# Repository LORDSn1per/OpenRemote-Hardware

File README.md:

# OpenRemote Rev6 Hardware

OpenRemote Rev6 is an open-source, offline smart remote based on the excellent [OMOTE hardware](https://github.com/OMOTE-Community/OMOTE-Hardware). It combines a 2.8-inch capacitive touchscreen with physical buttons, infrared, Wi-Fi, Bluetooth, an ESP32-S3, expandable storage, and a fully 3D-printable enclosure.

Rev6 focuses on making the remote easier to source, nicer to print, more serviceable, and ready for dock charging—while retaining support for the original Adafruit display.

> **Firmware:** [OpenRemote Firmware](https://github.com/LORDSn1per/OpenRemote-Firmware)

## What is new in Revision 6?

- **New IPS display support.** Rev6 supports the EastRising/BuyDisplay ER-TFT028A2-4 capacitive display with a separate six-pin touch FPC. It is brighter, sharper, has much better viewing angles, is still in production, and is free of the ghost-touch problem that affected the original screen.
- **Original display compatibility.** The discontinued Adafruit Product 2770/CH280QV10-CT display remains fully supported, and the Rev6 firmware includes an option that runs it with zero ghost touches.
- **Built-in microphone.** A rear-mounted digital I2S microphone provides hardware support for voice control, voice search, and future assistant features.
- **Faster charging.** The TP4056 charging circuit is configured for up to approximately 1 A, subject to the battery, power source, and thermal conditions.
- **Dock charging input.** Rev6 includes a dedicated 5 V input before the fuse, feeding the pogo-pin charging dock contacts or any other 5 V source.
- **Improved serviceability.** Five rear-installed M3 × 8 mm screws secure the PCB and enclosure, making the remote easier to assemble and reopen.
- **Updated PCB branding.** The board is now branded OpenRemote and includes a QR code linking directly to the firmware repository.

## New BuyDisplay LCD

### Why the display changed

Two things forced the move away from the original Adafruit screen:

1. **It is discontinued.** The Adafruit Product 2770 / CH280QV10-CT is no longer in production. Anyone building a remote today is hunting through dwindling stock and resellers, which is no basis for a project people are meant to be able to build.
2. **Its touch behaviour could make the remote unusable.** The Adafruit panel is subject to a well-known ghost-touch problem — phantom presses the user never made. On a remote control that is not a cosmetic annoyance: the device wakes by itself, fires commands at your equipment, and drains its own battery.

The recommended Rev6 screen is therefore the 2.8-inch 240×320 EastRising/BuyDisplay IPS TFT with capacitive touch. It is in current production, easier to source, brighter and sharper, has far better viewing angles, and does not suffer the ghost-touch fault. Its separate six-pin touch cable connects to the new J6 connector on the Rev6 PCB.

### The Adafruit display still works — with zero ghost touches

If you already own the Adafruit panel, it is not wasted. The Rev6 firmware includes an option that changes how the Adafruit touch panel is handled, and with it enabled the display produces **zero ghost touches**. It is a fully supported configuration, not a fallback, and it is why the Adafruit cover plate and matching printed parts are still published here.

Choose your display on this basis:

- **Building from scratch, or buying a screen now** — use the BuyDisplay panel. It is the current, in-production part.
- **Already have the Adafruit panel** — use it, enable the Adafruit touch option in the firmware, and print the Adafruit cover plate.

Either way, set the correct display option in the [OpenRemote firmware](https://github.com/LORDSn1per/OpenRemote-Firmware) before use.

### Fitting

The BuyDisplay assembly is approximately **0.8 mm thicker** than the original Adafruit screen. It therefore requires the newly updated BuyDisplay front cover plate. Do not try to force the thicker display into the original Adafruit cover.

Printable parts are split by display, so each folder contains a complete, matched set:

- [`CAD/BuyDisplay LCD/`](CAD/BuyDisplay%20LCD) — use **`Cover Plate 5mm (+1mm) Rev6-v37.stl`** with the new BuyDisplay screen.
- [`CAD/Adafruit LCD/`](CAD/Adafruit%20LCD) — use **`Cover Plate 4mm (+0mm) Rev6-v37.stl`** with the original Adafruit screen.

Each folder also carries a **Bambu Lab 3MF project** prepared for multicolour printing.

| BuyDisplay screen | New and original screens |
|:---:|:---:|
|  |  |

## Redesigned printed buttons

The Rev6 button system has been redesigned for a cleaner, more professional finish:

- The button grid now prints as **two interlocking halves** that click together.
- Separating the grid makes multicolour button graphics easier to print cleanly.
- Button faces are now completely smooth.
- The old physical cut-outs used to form button icons have been removed.
- Icons and labels can instead be printed directly into the smooth button surfaces for sharper graphics and a much nicer feel.
- The supplied Bambu Lab 3MF project contains the prepared colour-printing setup.

## Rear-case options

The Rev6 enclosure is available with two rear-shell choices:

1. **Normal rear case** — the standard shell for USB-C charging (`Case - Screws and No Pogo Pins Rev6-v37.stl`).
2. **Pogo-pin rear case** — adds two charging contacts for the self-aligning charging dock (`Case - Screws with Pogo Pins Rev6-v37.stl`).

The spring-loaded pogo pins live in the dock; the remote carries fixed gold-plated contacts, so there is nothing sprung to wear out in the handheld part.

## Charging dock

<div align="center">
  
</div>

The Rev6 charging dock is a self-aligning cradle that charges the remote through the pogo-pin rear case, and doubles as an always-on IR and sub-GHz blaster in its own right.

- **Pogo-pin charging.** Two spring-loaded pins meet the fixed contacts in the pogo rear case, so the remote charges by being set down rather than plugged in.
- **Independent ESP32-C3.** An ESP32-C3 Super Mini gives the dock its own Wi-Fi and Bluetooth, so it can act while the remote is asleep or away from the cradle.
- **Four-emitter IR blaster.** Four MHL512IR059CRT 940 nm emitters run in parallel, each through its own 39 Ω 0.5 W resistor, switched by an FS8205A dual MOSFET. Designed for roughly 95 mA per emitter in pulsed remote-control service, giving the dock far more IR reach than the handheld unit.
- **433 MHz sub-GHz radio.** A CC1101 module on SPI adds control of RF devices that infrared cannot reach — blinds, garage doors, and similar.
- **Status LED and button.** A tactile button on GPIO3 with hardware debounce, plus a status indicator.
- **Powered by USB-C.** The dock is powered solely through the USB-C connector on the ESP32-C3 module. The 2-pin JST header (J1) is not a second power input — it carries the 5 V rail out to the pogo pins.
- **Serviceable.** A 45 × 60 mm two-layer PCB on a 37 × 52 mm M3 mounting pattern, with a separate printed base lid.
- **Smart-home relay.** Because the board has its own Wi-Fi it can hold a permanent connection to Home Assistant, an MQTT broker or Homebridge, and act on the remote's behalf while the remote sleeps. That is a firmware capability rather than a hardware one — see the [firmware repository](https://github.com/LORDSn1per/OpenRemote-Firmware) — but it is the reason the dock carries an ESP32-C3 rather than a charging circuit alone.

> **Firmware note:** the IR bank is sized for pulsed use. Firmware must not hold `IR_PWM` high continuously.

### Dock files

- Printable parts: [`CAD/Dock/STL`](CAD/Dock/STL) — dock shell, base lid, and menu button, plus a Bambu Lab 3MF project in [`CAD/Dock`](CAD/Dock).
- Fusion source: [`CAD/Charging Dock Rev6-v47.f3z`](CAD/Charging%20Dock%20Rev6-v47.f3z)
- KiCad source: [`PCB/Dock Rev6`](PCB/Dock%20Rev6) — includes its own [project README](PCB/Dock%20Rev6/README.md) covering footprints, sourcing notes, and the Fusion handoff transform.
- Production files: [Gerber and drill ZIP](PCB/Dock%20Rev6/Production%20Files/gerber.zip), [CPL](PCB/Dock%20Rev6/Production%20Files/CPL.csv) and [BOM](PCB/Dock%20Rev6/Production%20Files/BOM.xlsx) for JLCPCB assembly of the SMD parts. The through-hole parts — ESP32-C3 headers, CC1101, IR LEDs, resistors, button, J1 and C6 — are fitted by hand.

## PCB files

The complete KiCad source is in [`PCB/Revision 6`](PCB/Revision%206). Custom symbols, footprints, and 3D models are included with the project.

The exact production files prepared for the Rev6 manufacturing order are here:

- [Gerber and drill ZIP](PCB/Revision%206/PCB%20Production%20Files/gerber.zip)
- [Component placement list (CPL)](PCB/Revision%206/PCB%20Production%20Files/CPL.csv)
- [Bill of materials (BOM)](PCB/Revision%206/PCB%20Production%20Files/BOM.xlsx)

The PCB is a two-layer design. The production set was exported using the **EastRising Capacitive LCD** assembly variant. The original Adafruit display remains represented in the KiCad project as an alternate variant.

> MIC1, the microphone module, does not currently have a JLCPCB/LCSC placement code in the production BOM. Source and fit it separately if your assembler cannot supply it.

## Core hardware features

- ESP32-S3 with Wi-Fi and Bluetooth
- 2.8-inch 240×320 capacitive touchscreen
- Physical navigation, media, volume, channel, activity, and colour buttons
- High-power infrared output
- MicroSD storage
- Motion-based wake support
- Built-in I2S microphone
- USB-C charging
- Pogo-pin dock charging
- Fully local operation with no mandatory cloud service

## Building the remote

1. Order the Rev6 PCB using the supplied Gerber ZIP, BOM, and CPL.
2. Source the selected LCD and use its matching front cover plate.
3. Print the enclosure and buttons. For multicolour printing, use the supplied Bambu Lab 3MF project.
4. Fit a suitable protected 3.7 V LiPo battery with the correct JST polarity.
5. Install the PCB and secure the assembly using five M3 × 8 mm screws.
6. Flash the latest [OpenRemote firmware](https://github.com/LORDSn1per/OpenRemote-Firmware).

Always verify component orientation, battery polarity, display selection, and the manufacturer preview before ordering assembled PCBs.

## Project status

The Rev6 remote PCB has been manufactured and assembled, and the first unit is running. The normal and pogo-pin rear cases and both display cover plates are complete and published.

The charging dock's enclosure parts are complete and published. Its PCB has been corrected — the ESP32-C3 Super Mini now mounts on the underside of the board — and a new set of fabrication files is published. The corrected dock board has not yet been built and tested, so check the manufacturer preview carefully before ordering.

## Credits

OpenRemote builds on the original open-source [OMOTE](https://github.com/OMOTE-Community) hardware project. Thank you to the OMOTE contributors and community for creating the foundation that made OpenRemote possible.

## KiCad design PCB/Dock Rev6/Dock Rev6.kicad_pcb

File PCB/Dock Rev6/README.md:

# OpenRemote Dock Rev6 KiCad Project

This is a self-contained KiCad 10 project starter for the OpenRemote Rev6 charging dock.

## Included footprints and 3D models

| Library footprint | Intended hardware | Interface / package |
|---|---|---|
| `ESP32-C3_SuperMini_Header_2x08_P2.54mm` | ESP32-C3 Super Mini shown by the owner | Two 1x8 headers, 2.54 mm pitch; owner-supplied STEP model |
| `CC1101_433MHz_Coil_Module_2x04_P2.54mm` | 28x15 mm CC1101 433 MHz module, spring antenna version | 2x4 header, 2.54 mm pitch |
| `LED_5mm_Side_Mount_C405273` | Meihua MHL512IR059CRT IR LED, LCSC C405273 | THT, 5 mm, horizontal/side mounting |
| `FS8205A_SOT-23-6` | FUXINSEMI FS8205A, LCSC C908265 | SOT-23-6 |
| `HX-XH2.54-2PZZ_C42391660` | hanxia HX-XH2.54-2PZZ, LCSC C42391660 | Vertical shrouded 1x2 male header; vendor land pattern is 2.50 mm pitch |
| `SW_6x6x5H_THT` | 6x6 mm tactile switch, 5 mm body height | Four-pin THT |
| `LED_5mm_Green_THT` | Standard green 5 mm LED | THT, 2.54 mm pitch |

The ESP32 model is the owner's supplied `esp32 c3 supermini.step`, copied into the project as `ESP32-C3_SuperMini.step`. The project also includes `ESP32-C3_SuperMini_2x08_Header.step`: two 2.24 mm-high black 1x8 header blocks with 16 gold pins. All STEP files are project-local, so no Downloads or global KiCad 3D-model path is required.

## Important sourcing notes

- The ESP module follows the owner's supplied **16-pin ESP32-C3 Super Mini** image: 18x22.52 mm with two 1x8, 2.54 mm header rows. It does not use the different 18-pin Waveshare C3-Zero footprint from the earlier retail link.
- J1 is the exact hanxia HX-XH2.54-2PZZ sold as LCSC C42391660. LCSC describes it as 2.54 mm, but its manufacturer-linked EasyEDA land pattern uses 2.50 mm pad pitch, 1.0 mm drills, and a 7.5 x 5.9 mm shrouded body; the project follows that land pattern.
- CC1101 clone modules vary. This footprint follows the common 28x15 mm, 2x4 2.54 mm module and the pin order shown in the provided image. Check the delivered module before ordering the PCB.
- `Dock Rev6.kicad_pcb` uses a 45x60 mm main body with narrow front and rear tongues. The confirmed physical rear tongue ends at dock Z=`-68.0 mm`; it is straight between the two rear receivers and has no obsolete scallops.
- The owner confirmed that the provisional handoff reversed the physical faces. The installed-board mapping is now **physical dock Z = KiCad Y - 140 mm**: Fusion Z=`-70` is the rear and Z=`+30` is the front.
- U1 is centred at KiCad `(100.00, 82.39)` with USB-C facing the physical rear and is placed on `B.Cu`. The ESP32 module hangs below the host PCB; the black header plastic lies between the ESP32 board and the host PCB, as it will when assembled with female header sockets. It was moved 1.5 mm into the cavity so the module PCB clears the rear wall. Its exact 18 mm body has approximately 0.50 mm lateral clearance to each physical rear lid receiver.
- The four large `User.Drawings` circles are the exact **15 mm OD physical receiver outlines**, mirrored into the confirmed board coordinates. Rear centres are KiCad `(82.998, 80.858)` and `(117.002, 80.858)`; front centres are `(83.643, 161.292)` and `(116.357, 161.292)`.
- In Fusion, `Dock + Correct Rear USB-C Opening Base Feature` was removed and the retained master body was restored as the visible solid `Dock - User Editable Shell (No Cutouts)`. This leaves the enclosure apertures for the owner to sketch and cut directly without deleting the dock shell.
- The final exact-solid Fusion audit reports **no collision between the underside ESP32/header assembly and the base lid or its bosses**. The lowest point of the ESP32 model is 0.294 mm above the flat lid surface. The USB, button, and LED apertures are intentionally left for the owner to create before enclosure release.
- Four 3.3 mm NPTH M3 mounting holes are on an exact 37x52 mm pattern at dock X/Z `(+/-18.5, +6)` and `(+/-18.5, -46)`. Each hole has an R4 mm all-copper keepout. H1-H4 are locked `board_only` footprints, excluded from BOM and position files, so **Update PCB from Schematic will not delete them again**.
- The matching Fusion base lid has four 7.5 mm OD bosses at those same centres. Each boss has a 2.55 mm blind pilot, an 8.0 mm PCB seating plane, and 3.4 mm thread engagement for an M3x5 screw through this 1.6 mm board. The original pre-boss lid body is retained hidden for rollback.

## Pin order

CC1101 pads are numbered by rows as shown in the supplied diagram: `1 GND`, `2 VCC`, `3 GDO0`, `4 CSN`, `5 SCK`, `6 MOSI`, `7 MISO/GDO1`, `8 GDO2`.

ESP32-C3 Super Mini pad numbers use the printed signal names directly. USB-C is at the top: left row `5V`, `GND`, `3V3`, `GPIO4/SCK/A4`, `GPIO3/A3`, `GPIO2/A2`, `GPIO1/A1`, `GPIO0/A0`; right row `GPIO5/MISO/A5`, `GPIO6/MOSI`, `GPIO7/SS`, `GPIO8/SDA`, `GPIO9/SCL`, `GPIO10`, `GPIO20/RX`, `GPIO21/TX`.

## Electrical design

- CC1101 SPI: `GPIO4 SCK`, `GPIO5 MISO`, `GPIO6 MOSI`, `GPIO7 CSN`; interrupts are `GPIO10 GDO0` and `GPIO20 GDO2`.
- Four MHL512IR059CRT emitters are connected in parallel through individual `39R 0.5W` resistors. GPIO0 drives both paralleled halves of Q1 through `100R`, with a `100k` gate pulldown.
- The 39R IR branches are designed for pulsed remote-control service at approximately 95mA per LED from 5V. Firmware must not hold `IR_PWM` high continuously.
- The green status LED uses GPIO1 and `1k`. The tactile button uses GPIO3 with a `10k` pull-up and `100nF` hardware debounce.
- ESP32-C3 strap pins GPIO2, GPIO8, and GPIO9 are deliberately left unconnected; GPIO21 is also reserved.
- Added decoupling: `100nF + 10uF` at the ESP 5V input, `100nF + 10uF` at the CC1101 3.3V rail, and `100uF + 100nF` at the pulsed IR bank.

### Pogo-pin output protection

`F1` is a 1 A resettable polyfuse (PPTC, LCSC C220146,
`DockRev6:Fuse_1206_3216Metric_Pad1.42x1.75mm_HandSolder`) in series between the `+5V`
rail and `J1` pin 1, creating the `POGO_5V` net. It is the same part the remote uses as
its F1. The IR bank, the ESP32 and the decoupling all stay on the raw `+5V` rail; only
the pogo output passes through the fuse.

**It is in the schematic only — it is not yet placed or routed on the PCB.**

This replaced an earlier BAT20J series diode, for two reasons. A polyfuse actually
addresses the failure being guarded against: if the exposed pogo contacts are shorted,
it heats and trips, where a series diode would simply conduct and let the rail collapse.
And it barely drops any voltage — a few tens of millivolts against roughly 0.45 V for a
Schottky at 1 A — so the remote still sees close to a full 5 V.

Two things to be aware of:

- A polyfuse does **not** block reverse current. The dropped diode would have stopped
  the remote back-feeding into the dock; the fuse does not. If back-feed matters, an
  ideal-diode controller or a load switch would cover both cases.
- Trip is thermal, so it takes seconds rather than being instant, and hold current
  derates as temperature rises. With the remote's TP4056 set near 1 A, a 1 A hold part
  sits close to its limit inside a closed enclosure. Watch for nuisance trips during a
  full-rate charge; a 1.1 A or 1.5 A hold part is the fallback.

### Capacitor placement

- `C1 100nF`: immediately beside U1's 5V/GND header pins; shortest possible loop.
- `C2 10uF`: beside U1 and C1 on the 5V rail; C1 should be closer than C2.
- `C3 100nF`: immediately beside U2 pins 2 VCC and 1 GND; this is the most placement-sensitive radio capacitor.
- `C4 10uF`: beside U2 and C3; C3 should be closer than C4.
- `C5 100nF`: beside U1 GPIO3 and pull-up R1, at the controller end of the BUTTON trace.
- `C6 100uF`: beside Q1/J1 at the high-current IR power entry/current loop.
- `C7 100nF`: beside Q1/J1 and C6, with the shortest 5V-to-GND loop; C7 should be closer to the switching loop than C6.

`Dock Rev6.kicad_pcb` is populated but not routed. The remaining SMD parts are staged by circuit: C1/C2 beside the header-mounted ESP32, C5/R1 immediately left of it, C3/C4 beside the CC1101 power pins, R3/R4/Q1 to the left of the CC1101 coil envelope, C7 beside J1, and R2 beside D5. The current DRC reports silkscreen cleanup warnings plus the expected unrouted nets; it does not report a copper short, hole, or board-edge clearance failure.

The `.before-*` rollback boards, the DRC/ERC reports, the netlist and the exported schematic PDF have been removed; only the current `Dock Rev6.kicad_pcb` and `Dock Rev6.kicad_sch` are kept. Earlier states remain in git history if a rollback is ever needed. `apply_mechanical_fit_v3.py` reapplies the final U1 position and rear-tongue geometry without altering nets or component identities. Use KiCad's native refill after running it. Do not run `generate_dock_rev6_mechanical_board.py` on the populated board; that generator creates a blank mechanical PCB and would replace component placement.

## Fusion 3D handoff

`Dock Rev6 PCB Assembly.step` is the current board-plus-components model handed to
Fusion. Regenerate it with `export_dock_rev6_step.py`, which runs:

```
kicad-cli pcb export step --subst-models --no-dnp --force
```

No origin flag is passed, so the STEP keeps KiCad's absolute board coordinates
(substrate spans X `77.5`-`122.5`, Y `-166.0`-`-72.0`, Z `0`-`1.6`). The Fusion
placement transform depends on that:

```
dock X =  step X - 100 mm
dock Y =  step Z + 8 mm      (PCB seating plane on the base-lid bosses)
dock Z = -step Y - 140 mm    (owner-confirmed mirrored physical face)
```

`CAD/FusionScripts/DockRev6PCBReplace` deletes any existing `Dock Rev6 PCB*`
occurrence, re-imports this STEP at that transform as the component
`Dock Rev6 PCB`, then re-runs the solid interference check against `Dock:1` and
`Dock Base Lid:1` and writes `CAD/Dock Rev6/Charging Dock Rev6 PCB Replace Report.json`.
Base-lid interference is a failure; dock-shell interference at SW1, J1, D1-D5 is
expected until the owner cuts the USB, button, and LED apertures.

`Dock Rev6 Component Staging.step` is the superseded 26 Aug 16:52 export, taken
before power/ground routing was finalised and before SW1 moved to the
`SW-TH_KH-6X6X5H-ZJ` (C2837541) model and J1 to `HX-XH2.54-2PZZ` (C42391660). It
is kept only for rollback; Fusion should no longer import it.

`Dock Rev6 PCB Assembly Preview.png` and `Dock Rev6 PCB Assembly Preview Bottom.png`
are `kicad-cli pcb render` views of the same board state.

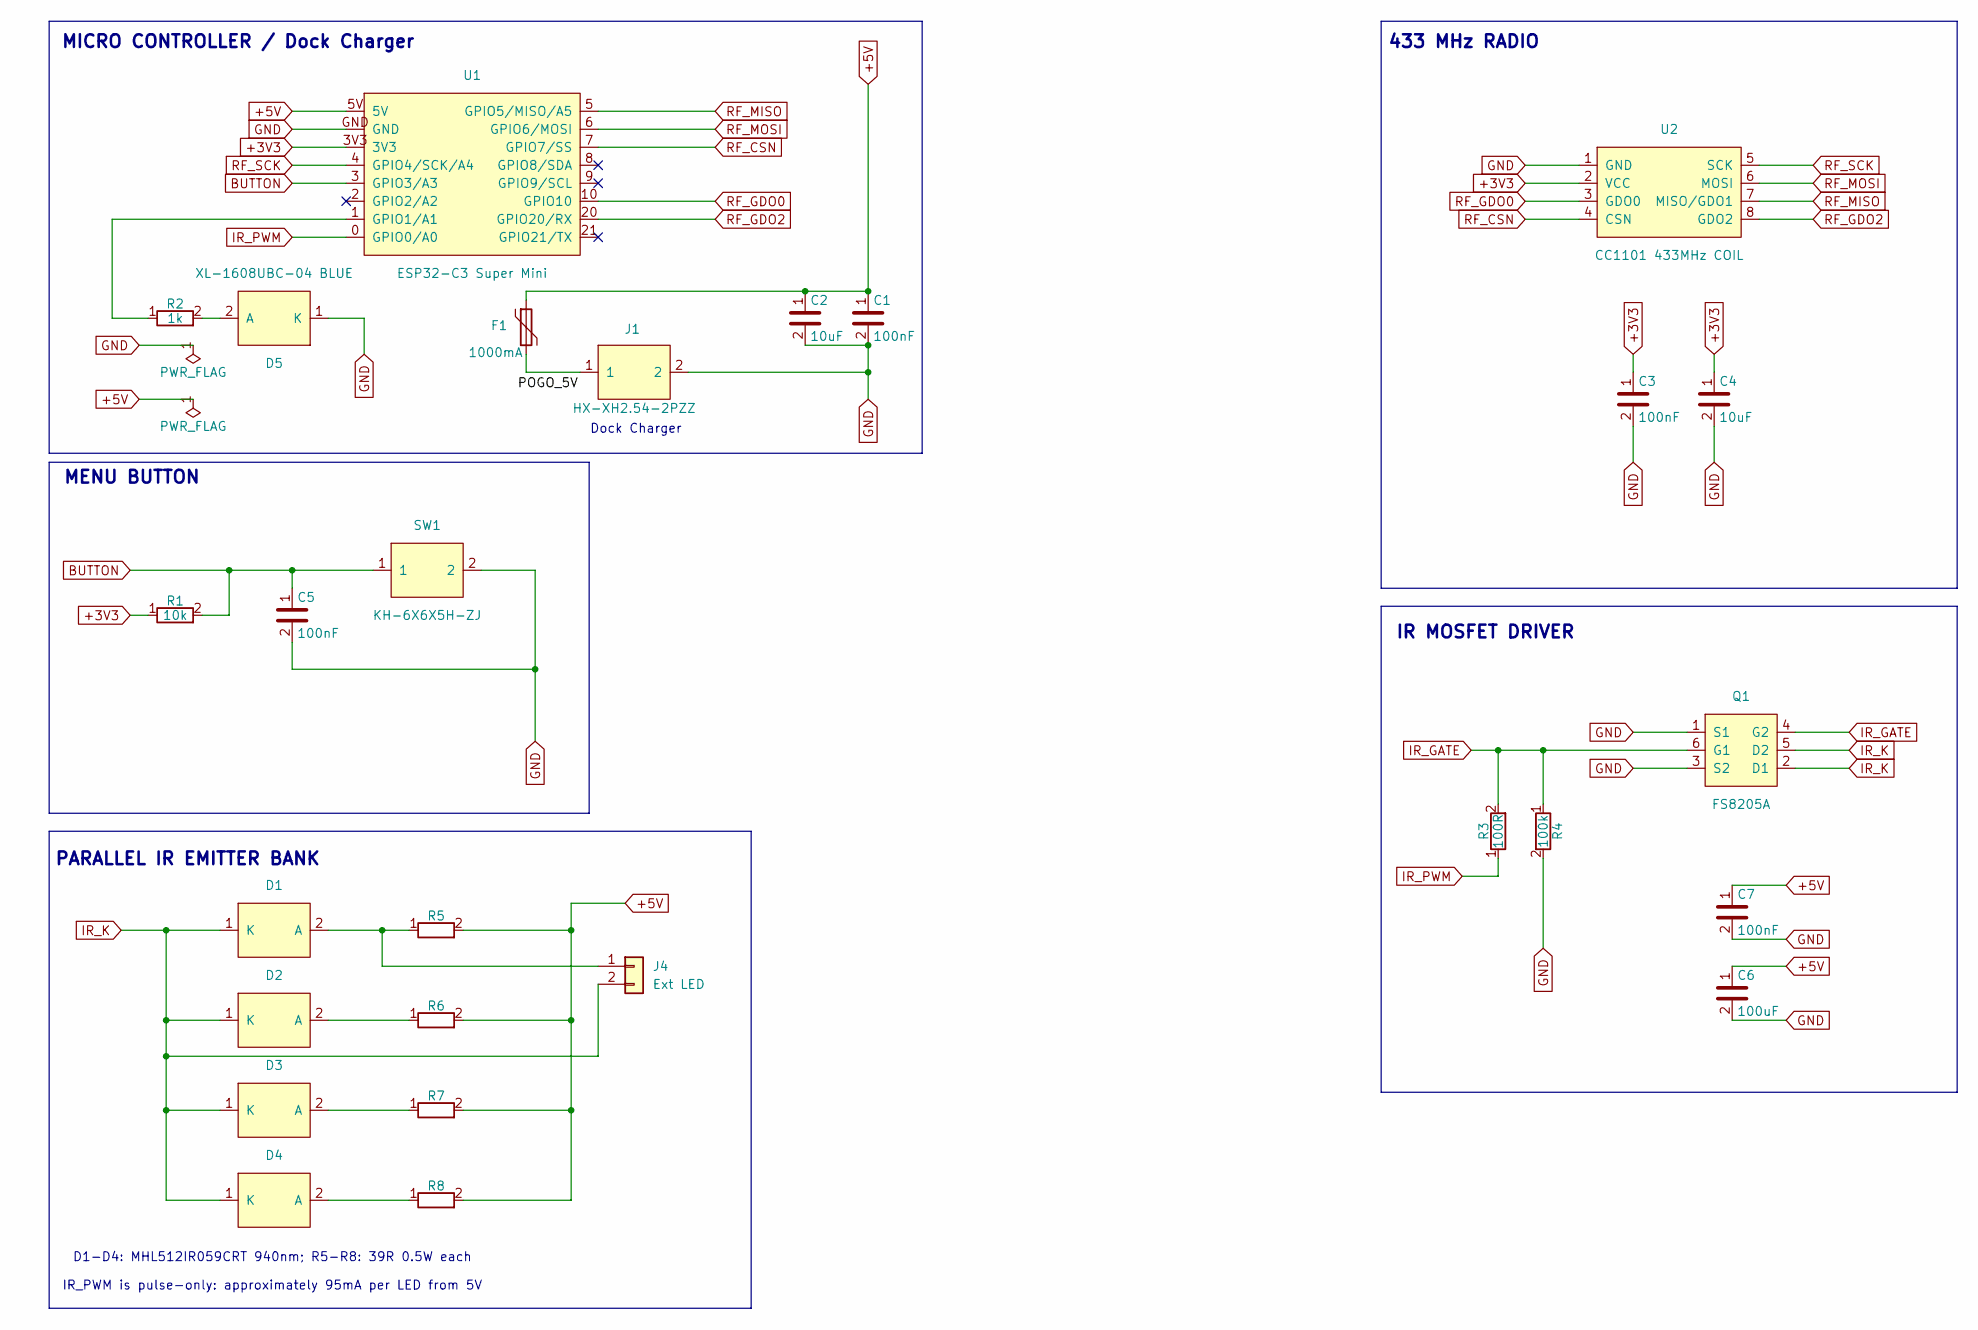
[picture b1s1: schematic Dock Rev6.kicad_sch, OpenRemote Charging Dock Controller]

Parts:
C1, C3, C5, C7: 100nF; C_0603_1608Metric
C2, C4: 10uF; C_0805_2012Metric
C6: 100uF; CP_Radial_D5.0mm_P2.50mm
D1: MHL512IR059CRT 940nm; IR_LED_THT_D1_with_Assembly3D
D2, D3, D4: MHL512IR059CRT 940nm; LED_5mm_Green_THT
D5: XL-1608UBC-04 BLUE; LED_0603_1608Metric_NoSilk; LCSC C965807
F1: 1000mA; Fuse_1206_3216Metric_Pad1.42x1.75mm_HandSolder; LCSC C220146
J1: HX-XH2.54-2PZZ; HX-XH2.54-2PZZ_C42391660
J4: Ext LED; R_0508_1220Metric_Pad1.12x2.15mm_HandSolder
Q1: FS8205A; FS8205A_SOT-23-6
R1: 10k; R_0603_1608Metric
R2: 1k; R_0603_1608Metric
R3: 100R; R_0603_1608Metric
R4: 100k; R_0603_1608Metric
R5, R6, R7, R8: 39R 0.5W; R_Axial_DIN0411_L9.9mm_D3.6mm_P15.24mm_Horizontal
SW1: KH-6X6X5H-ZJ; SW-TH_KH-6X6X5H-ZJ
U1: ESP32-C3 Super Mini; ESP32-C3_SuperMini_Header_2x08_P2.54mm
U2: CC1101 433MHz COIL; CC1101_433MHz_Coil_Module_2x04_P2.54mm

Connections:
+3V3: C3.1, C4.1, R1.1, U1.3V3, U2.2 (VCC)
+5V: C1.1, C2.1, C6.1, C7.1, F1.1, R5.2, R6.2, R7.2, R8.2, U1.5V
BUTTON: C5.1, R1.2, SW1.1, U1.3 (GPIO3/A3)
GND: C1.2, C2.2, C3.2, C4.2, C5.2, C6.2, C7.2, D5.1 (K), J1.2, Q1.1 (S1), Q1.3 (S2), R4.2, SW1.2, U1.GND, U2.1 (GND)
IR_GATE: Q1.4 (G2), Q1.6 (G1), R3.2, R4.1
IR_K: D1.1 (K), D2.1 (K), D3.1 (K), D4.1 (K), J4.2, Q1.2 (D1), Q1.5 (D2)
IR_PWM: R3.1, U1.0 (GPIO0/A0)
unnamed: D1.2 (A), J4.1, R5.1
unnamed: D2.2 (A), R6.1
unnamed: D3.2 (A), R7.1
unnamed: D4.2 (A), R8.1
unnamed: D5.2 (A), R2.2
unnamed: F1.2, J1.1
unnamed: R2.1, U1.1 (GPIO1/A1)
RF_CSN: U1.7 (GPIO7/SS), U2.4 (CSN)
RF_GDO0: U1.10 (GPIO10), U2.3 (GDO0)
RF_GDO2: U1.20 (GPIO20/RX), U2.8 (GDO2)
RF_MISO: U1.5 (GPIO5/MISO/A5), U2.7 (MISO/GDO1)
RF_MOSI: U1.6 (GPIO6/MOSI), U2.6 (MOSI)
RF_SCK: U1.4 (GPIO4/SCK/A4), U2.5 (SCK)

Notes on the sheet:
PARALLEL IR EMITTER BANK
D1-D4: MHL512IR059CRT 940nm; R5-R8: 39R 0.5W each
IR MOSFET DRIVER
IR_PWM is pulse-only: approximately 95mA per LED from 5V
MENU BUTTON
433 MHz RADIO
Dock Charger
MICRO CONTROLLER / Dock Charger

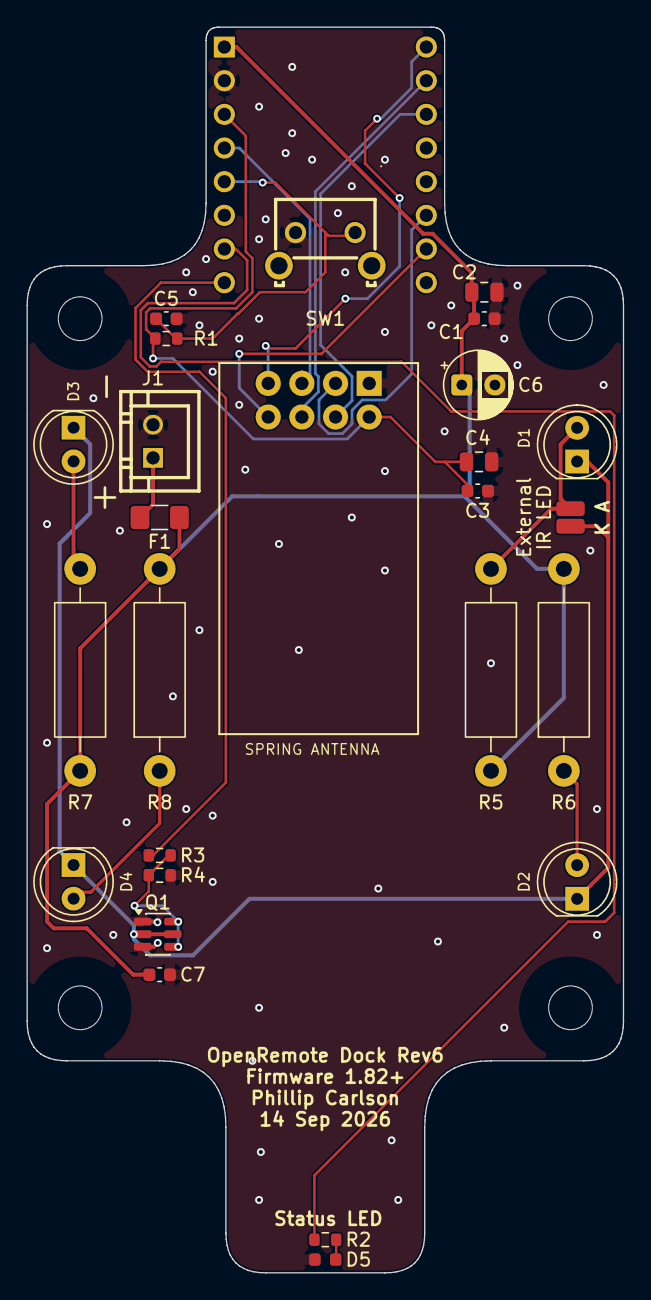
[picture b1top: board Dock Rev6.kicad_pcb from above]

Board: 2 copper layers, 45.0 x 94.0 mm, 31 parts (1 on the bottom side), 20 nets.

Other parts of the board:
H1, H2, H3, H4: M3x5 PCB SCREW / 3.3mm NPTH; MountingHole_3.2mm_M3

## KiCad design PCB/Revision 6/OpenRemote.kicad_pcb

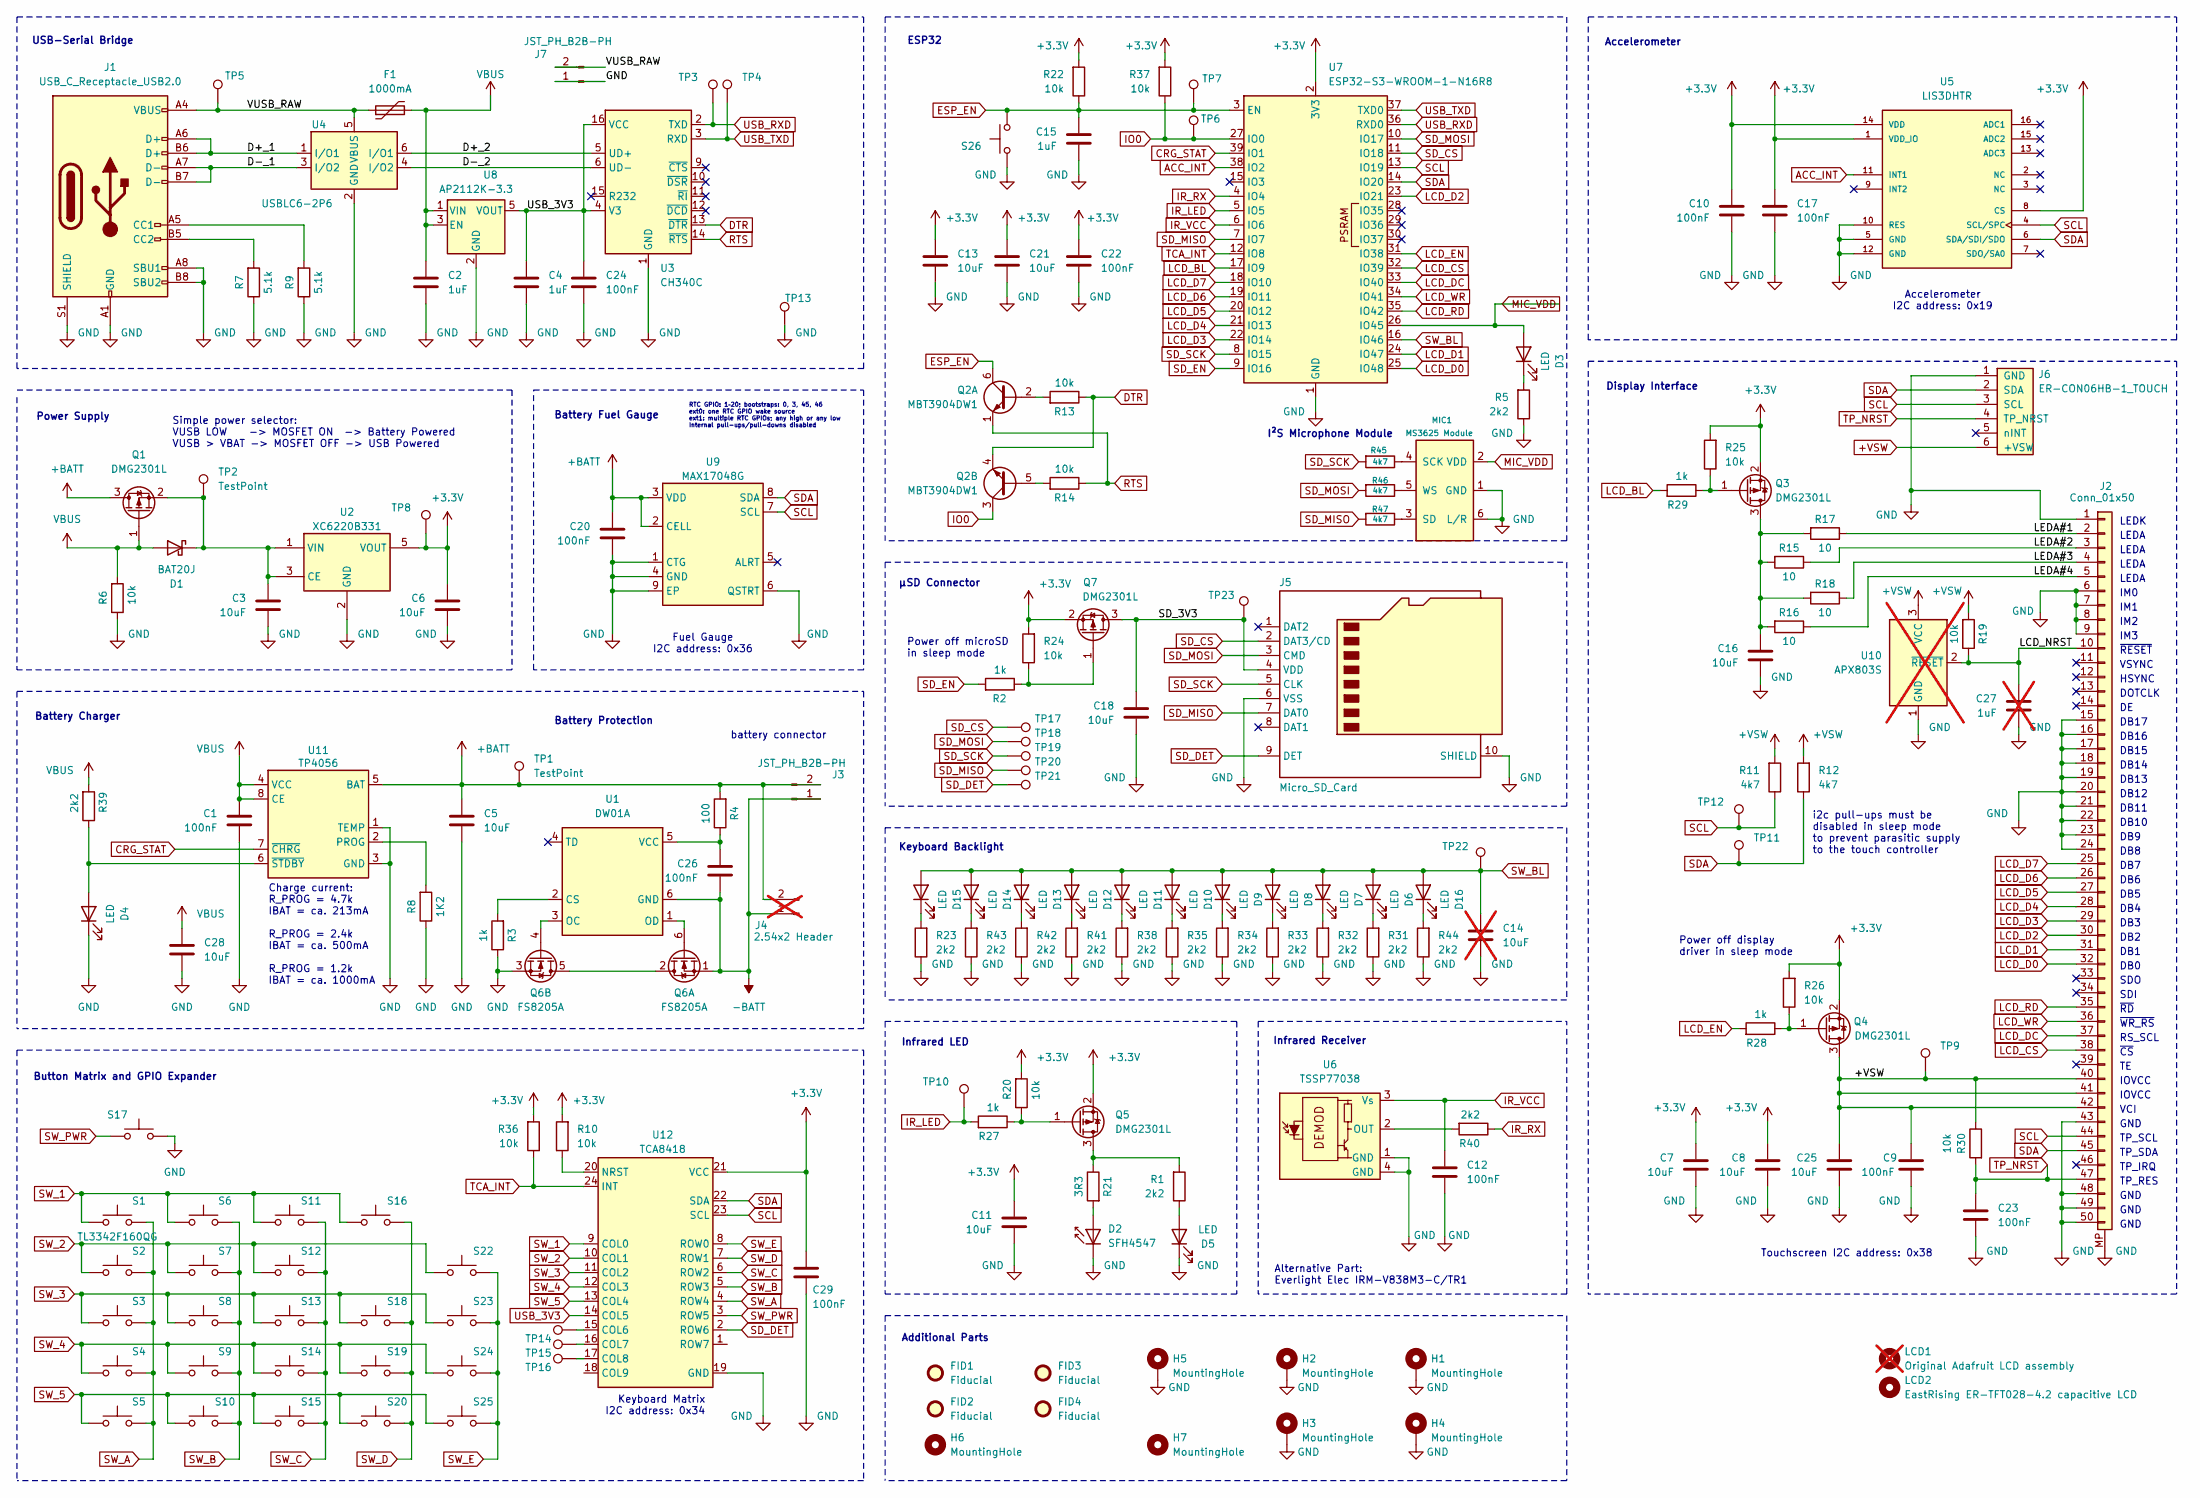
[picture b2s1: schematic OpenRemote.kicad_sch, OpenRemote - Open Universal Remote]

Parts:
C1, C9, C10, C12, C17, C20, C22, C23, C24, C26, C29: 100nF; C_0603_1608Metric; LCSC C1591
C2, C4, C15: 1uF; C_0603_1608Metric; LCSC C15849
C3, C5, C6, C7, C8, C11, C13, C16, C18, C21, C25, C28: 10uF; C_0805_2012Metric; LCSC C15850
C14: 10uF; C_0805_2012Metric; LCSC C15850; not fitted
C27: 1uF; C_0603_1608Metric; not fitted
D1: BAT20J; D_SOD-323; LCSC C49238173
D2: SFH4547; LED_5mm_Side_Mount; LCSC C405273
D3, D4, D5: LED; LED_0603_1608Metric; LCSC C965807
D6, D7, D8, D9, D10, D11, D12, D13, D14, D15, D16: LED; LED_0603_1608Metric; LCSC C84265
F1: 1000mA; Fuse_1206_3216Metric_Pad1.42x1.75mm_HandSolder; LCSC C220146
FID1, FID2, FID3, FID4: Fiducial; Fiducial_1mm_Mask2mm
H1, H2, H3, H5: MountingHole; MountingHole_3.2mm_M3_Pad_Via
H4: MountingHole; MountingHole_3.2mm_M3
H6, H7: MountingHole; MountingHole_2.5mm
J1: USB_C_Receptacle_USB2.0; USB_C_Receptacle_HRO_TYPE-C-31-M-12; LCSC C2982555
J2: Conn_01x50; TFT_2.83IN_240X320_50PIN; LCSC C11098
J3, J7: JST_PH_B2B-PH; JST_PH_B2B-PH-SM4-TB_1x02-1MP_P2.00mm_Vertical; LCSC C160352
J4: 2.54x2 Header; PinHeader_1x02_P2.54mm_Vertical; not fitted
J5: Micro_SD_Card; MicroSD Slot TF-01A; LCSC C20613191
J6: ER-CON06HB-1_TOUCH; ER-CON06HB-1_Compatible_1x06_P0.50mm_BottomContact; LCSC C202118
LCD1: Original Adafruit LCD assembly; Adafruit_280QV10_MECHANICAL; not fitted
LCD2: EastRising ER-TFT028-4.2 capacitive LCD; ER-TFT028-4.2_MECHANICAL
MIC1: MS3625 Module; MS3625_Module_Back_Mount_SMD
Q1, Q3, Q4, Q5, Q7: DMG2301L; SOT-23; LCSC C102619
Q2: MBT3904DW1; SOT-363_SC-70-6; LCSC C110150
Q6: FS8205A; SOT-23-6; LCSC C908265
R1, R5, R23, R31, R32, R33, R34, R35, R38, R39, R40, R41, R42, R43, R44: 2k2; R_0603_1608Metric; LCSC C114662
R2, R3, R27, R28, R29: 1k; R_0603_1608Metric; LCSC C22548
R4: 100; R_0603_1608Metric; LCSC C125923
R6, R10, R13, R14, R19, R20, R22, R24, R25, R26, R30, R36, R37: 10k; R_0603_1608Metric; LCSC C98220
R7, R9: 5.1k; R_0603_1608Metric; LCSC C105580
R8: 1K2; R_0603_1608Metric; LCSC C22765
R11, R12: 4k7; R_0603_1608Metric; LCSC C99782
R15, R16, R17, R18: 10; R_0603_1608Metric; LCSC C109318
R21: 3R3; R_0805_2012Metric; LCSC C313912
R45, R46, R47: 4k7; R_0603_1608Metric; LCSC C23162
S1, S2, S3, S4, S5, S6, S7, S8, S9, S10, S11, S12, S13, S14, S15, S16, S17, S18, S19, S20, S22, S23, S24, S25, S26: TL3342F160QG; SW_SPST_TL3342; LCSC C778172
TP1, TP2, TP3, TP4, TP5, TP6, TP7, TP8, TP9, TP10, TP11, TP12, TP13, TP14, TP15, TP16, TP17, TP18, TP19, TP20, TP21, TP22, TP23: TestPoint; TestPoint_Pad_D1.5mm
U1: DW01A; SOT-23-6; LCSC C18164398
U2: XC6220B331; SOT-23-5; LCSC C86534
U3: CH340C; SOIC-16_3.9x9.9mm_P1.27mm; LCSC C84681
U4: USBLC6-2P6; SOT-666; LCSC C2827693
U5: LIS3DHTR; XDCR_LIS3DHTR; PARTREV 2; LCSC C15134
U6: TSSP77038; Heimdall vertical; LCSC C3291489
U7: ESP32-S3-WROOM-1-N16R8; ESP32-S3-WROOM-1; LCSC C2913202
U8: AP2112K-3.3; SOT-23-5; LCSC C51118
U9: MAX17048G; TDFN-8-1EP_2x2mm_P0.5mm_EP0.8x1.2mm; LCSC C2682616
U10: APX803S; SOT-23; not fitted
U11: TP4056; Infineon_PG-DSO-8-27_3.9x4.9mm_EP2.65x3mm; LCSC C725790
U12: TCA8418; HVQFN-24-1EP_4x4mm_P0.5mm_EP2.5x2.5mm; LCSC C138713

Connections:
+3.3V: C6.1, C7.2, C8.2, C10.1, C11.2, C13.2, C17.1, C21.2, C22.1, C29.1, Q3.2 (S), Q4.2 (S), Q5.2 (S), Q7.2 (S), R10.2, R20.2, R22.2, R24.2, R25.2, R26.2, R36.2, R37.2, TP8.1 (1_1), U2.5 (VOUT), U5.1 (VDD_IO), U5.8 (CS), U5.14 (VDD), U7.2 (3V3), U12.21 (VCC)
+BATT: C5.2, C20.1, J3.2, J4.2, Q1.3 (D), R4.2, TP1.1 (1_1), U9.2 (CELL), U9.3 (VDD), U11.5 (BAT)
+VSW: C9.1, C25.2, J2.40, J2.41, J2.42 (Pin_41), J6.6 (+VSW), Q4.3 (D), R11.2, R12.2, R19.2, R30.1, TP9.1 (1_1), U10.3 (VCC)
-BATT: C26.2, J3.1, J4.1, Q6.1 (S), U1.6 (GND)
/D+_1: J1.A6 (D+), J1.B6 (D+), U4.1 (I/O1)
/D+_2: U3.5 (UD+), U4.6 (I/O1)
/D-_1: J1.A7 (D-), J1.B7 (D-), U4.3 (I/O2)
/D-_2: U3.6 (UD-), U4.4 (I/O2)
/LCD_NRST: C27.2, J2.10, R19.1, U10.2 (~RESET)
/LEDA#1: J2.2, R17.1
/LEDA#2: J2.3, R15.1
/LEDA#3: J2.4, R18.1
/LEDA#4: J2.5, R16.1
/SD_3V3: C18.2, J5.4 (VDD), Q7.3 (D), TP23.1 (1_1)
/VUSB_RAW: F1.1, J1.A4 (VBUS), J1.A9 (VBUS), J1.B4 (VBUS), J1.B9 (VBUS), J7.2, TP5.1 (1_1), U4.5 (VBUS)
ACC_INT: U5.11 (INT1), U7.38 (IO2)
CRG_STAT: U7.39 (IO1), U11.7 (~CHRG)
DTR: Q2.4 (E2), R13.1, U3.13 (~DTR)
ESP_EN: C15.2, Q2.6 (C1), R22.1, S26.2, TP7.1 (1_1), U7.3 (EN)
GND: C1.2, C2.2, C3.1, C4.2, C5.1, C6.2, C7.1, C8.1, C9.2, C10.2, C11.1, C12.2, C13.1, C14.1, C15.1, C16.1, C17.2, C18.1, C20.2, C21.1, C22.2, C23.1, C24.2, C25.1, C27.1, C28.1, C29.2, D2.1 (K), D4.1 (K), D5.1 (K), H1.1 (1_1), H2.1 (1_1), H3.1 (1_1), H4.1, H5.1 (1_1), J1.A1 (GND), J1.A8 (SBU1), J1.A12 (GND), J1.B1 (GND), J1.B8 (SBU2), J1.B12 (GND), J1.S1 (SHIELD), J2.1, J2.6, J2.7, J2.8, J2.9, J2.15, J2.16, J2.17, J2.18, J2.19, J2.20, J2.21, J2.22, J2.23, J2.24, J2.43, J2.48, J2.49, J2.50, J2.MP, J5.6 (VSS), J5.10 (SHIELD), J6.1 (GND), J7.1, MIC1.1 (GND), MIC1.6 (L/R), Q6.3 (S), R3.1, R5.1, R6.1, R7.1, R8.1, R9.1, R23.1, R31.1, R32.1, R33.1, R34.1, R35.1, R38.1, R41.1, R42.1, R43.1, R44.1, S17.1, S26.1, TP13.1 (1_1), U2.2 (GND), U3.1 (GND), U4.2 (GND), U5.5 (GND), U5.10 (RES), U5.12 (GND), U6.1 (GND), U6.4 (GND), U7.1 (GND), U7.40 (GND), U7.41 (GND), U8.2 (GND), U9.1 (CTG), U9.4 (GND), U9.6 (QSTRT), U9.9 (EP), U10.1 (GND), U11.1 (TEMP), U11.3 (GND), U11.9 (GND), U12.19 (GND)
IO0: Q2.3 (C2), R37.1, TP6.1 (1_1), U7.27 (IO0)
IR_LED: R27.2, TP10.1 (1_1), U7.5 (IO5)
IR_RX: R40.1, U7.4 (IO4)
IR_VCC: C12.1, U6.3 (Vs), U7.6 (IO6)
LCD_BL: R29.2, U7.17 (IO9)
LCD_CS: J2.38, U7.32 (IO39)
LCD_D0: J2.32, U7.25 (IO48)
LCD_D1: J2.31, U7.24 (IO47)
LCD_D2: J2.30, U7.23 (IO21)
LCD_D3: J2.29, U7.22 (IO14)
LCD_D4: J2.28, U7.21 (IO13)
LCD_D5: J2.27, U7.20 (IO12)
LCD_D6: J2.26, U7.19 (IO11)
LCD_D7: J2.25, U7.18 (IO10)
LCD_DC: J2.37, U7.33 (IO40)
LCD_EN: R28.2, U7.31 (IO38)
LCD_RD: J2.35, U7.35 (IO42)
LCD_WR: J2.36, U7.34 (IO41)
MIC_VDD: D3.2 (A), MIC1.2 (VDD), U7.26 (IO45)
unnamed: C3.2, D1.1 (K), Q1.2 (S), TP2.1 (1_1), U2.1 (VIN), U2.3 (CE)
unnamed: D2.2 (A), R21.2
unnamed: D3.1 (K), R5.2
unnamed: D4.2 (A), R39.1, U11.6 (~STDBY)
unnamed: D5.2 (A), R1.1
unnamed: D6.1 (K), R31.2
unnamed: D7.1 (K), R32.2
unnamed: D8.1 (K), R33.2
unnamed: D9.1 (K), R34.2
unnamed: D10.1 (K), R35.2
unnamed: D11.1 (K), R38.2
unnamed: D12.1 (K), R41.2
unnamed: D13.1 (K), R42.2
unnamed: D14.1 (K), R43.2
unnamed: D15.1 (K), R23.2
unnamed: D16.1 (K), R44.2
unnamed: J1.A5 (CC1), R9.2
unnamed: J1.B5 (CC2), R7.2
unnamed: MIC1.4 (SCK), R45.1
unnamed: MIC1.3 (SD), R47.1
unnamed: MIC1.5 (WS), R46.1
unnamed: Q2.2 (B1), R13.2
unnamed: Q2.5 (B2), R14.2
unnamed: C16.2, Q3.3 (D), R15.2, R16.2, R17.2, R18.2
unnamed: Q3.1 (G), R25.1, R29.1
unnamed: Q4.1 (G), R26.1, R28.1
unnamed: Q5.3 (D), R1.2, R21.1
unnamed: Q5.1 (G), R20.1, R27.1
unnamed: Q6.2 (D), Q6.5 (D)
unnamed: Q6.6 (G), U1.1 (OD)
unnamed: Q6.4 (G), U1.3 (OC)
unnamed: Q7.1 (G), R2.1, R24.1
unnamed: R3.2, U1.2 (CS)
unnamed: C26.1, R4.1, U1.5 (VCC)
unnamed: R40.2, U6.2 (OUT)
unnamed: R8.2, U11.2 (PROG)
unnamed: TP14.1 (1_1), U12.15 (COL6)
unnamed: TP15.1 (1_1), U12.16 (COL7)
unnamed: TP16.1 (1_1), U12.17 (COL8)
unnamed: R10.1, U12.20 (NRST)
RTS: Q2.1 (E1), R14.1, U3.14 (~RTS)
SCL: J2.44, J6.3 (SCL), R11.1, TP12.1 (1_1), U5.4 (SCL/SPC), U7.13 (IO19), U9.7 (SCL), U12.23 (SCL)
SDA: J2.45, J6.2 (SDA), R12.1, TP11.1 (1_1), U5.6 (SDA/SDI/SDO), U7.14 (IO20), U9.8 (SDA), U12.22 (SDA)
SD_CS: J5.2 (DAT3/CD), TP17.1 (1_1), U7.11 (IO18)
SD_DET: J5.9 (DET), TP21.1 (1_1), U12.2 (ROW6)
SD_EN: R2.2, U7.9 (IO16)
SD_MISO: J5.7 (DAT0), R47.2, TP20.1 (1_1), U7.7 (IO7)
SD_MOSI: J5.3 (CMD), R46.2, TP18.1 (1_1), U7.10 (IO17)
SD_SCK: J5.5 (CLK), R45.2, TP19.1 (1_1), U7.8 (IO15)
SW_1: S1.1, S6.1, S11.1, S16.1, U12.9 (COL0)
SW_2: S2.1, S7.1, S12.1, S22.1, U12.10 (COL1)
SW_3: S3.1, S8.1, S13.1, S18.1, S23.1, U12.11 (COL2)
SW_4: S4.1, S9.1, S14.1, S19.1, S24.1, U12.12 (COL3)
SW_5: S5.1, S10.1, S15.1, S20.1, S25.1, U12.13 (COL4)
SW_A: S1.2, S2.2, S3.2, S4.2, S5.2, U12.4 (ROW4)
SW_B: S6.2, S7.2, S8.2, S9.2, S10.2, U12.5 (ROW3)
SW_BL: C14.2, D6.2 (A), D7.2 (A), D8.2 (A), D9.2 (A), D10.2 (A), D11.2 (A), D12.2 (A), D13.2 (A), D14.2 (A), D15.2 (A), D16.2 (A), TP22.1 (1_1), U7.16 (IO46)
SW_C: S11.2, S12.2, S13.2, S14.2, S15.2, U12.6 (ROW2)
SW_D: S16.2, S18.2, S19.2, S20.2, U12.7 (ROW1)
SW_E: S22.2, S23.2, S24.2, S25.2, U12.8 (ROW0)
SW_PWR: S17.2, U12.3 (ROW5)
TCA_INT: R36.1, U7.12 (IO8), U12.24 (INT)
TP_NRST: C23.2, J2.47, J6.4 (TP_NRST), R30.2
USB_3V3: C4.1, C24.1, U3.4 (V3), U3.16 (VCC), U8.5 (VOUT), U12.14 (COL5)
USB_RXD: TP3.1 (1_1), U3.2 (TXD), U7.36 (RXD0)
USB_TXD: TP4.1 (1_1), U3.3 (RXD), U7.37 (TXD0)
VBUS: C1.1, C2.1, C28.2, D1.2 (A), F1.2, Q1.1 (G), R6.2, R39.2, U8.1 (VIN), U8.3 (EN), U11.4 (VCC), U11.8 (CE)

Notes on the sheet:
DB6
Accelerometer I2C address: 0x19
DB11
DB14
IM2
DB10
Infrared Receiver
Display Interface
LEDA
DB0
GND
DB16
Alternative Part: Everlight Elec IRM-V838M3-C/TR1
TP_RES
TP_IRQ
LEDK
IM1
IOVCC
Battery Fuel Gauge
~{RESET}
ESP32
RTC GPIO: 1–20; bootstraps: 0, 3, 45, 46 ext0: one RTC GPIO wake source ext1: multiple RTC GPIOs; any high or any low Internal pull-ups/pull-downs disabled
Battery Protection
IM3
DB5
Additional Parts
USB-Serial Bridge
Charge current: R_PROG = 4.7k IBAT = ca. 213mA R_PROG = 2.4k IBAT = ca. 500mA R_PROG = 1.2k IBAT = ca. 1000mA
DB17
TP_SDA
DB7
DB12
DB1
DOTCLK
~{WR_RS}
Infrared LED
µSD Connector
SDI
DB13
DB4

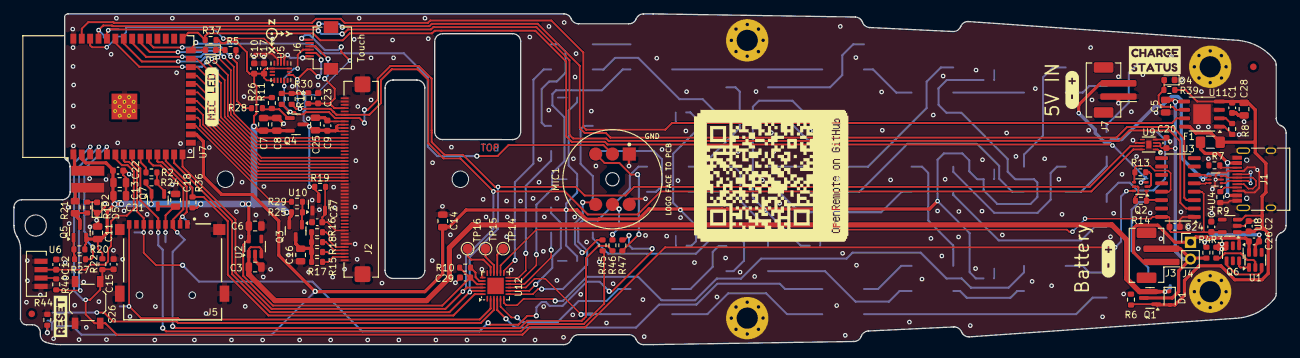
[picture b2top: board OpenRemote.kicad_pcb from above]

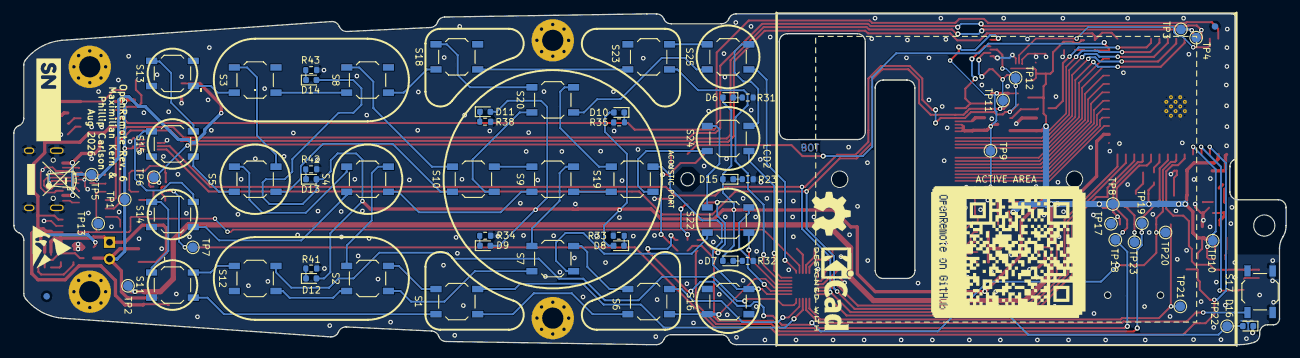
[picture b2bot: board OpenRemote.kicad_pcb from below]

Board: 2 copper layers, 192.4 x 50.0 mm, 191 parts (70 on the bottom side), 106 nets.

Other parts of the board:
MIC_LED_LABEL: MIC LED; MIC_LED_LABEL
OPENREMOTE_QR: https://github.com/LORDSn1per/OpenRemote-Firmware; OPENREMOTE_GITHUB_QR
OPENREMOTE_QR#2: https://github.com/LORDSn1per/OpenRemote-Firmware; OPENREMOTE_GITHUB_QR
kibuzzard-63D97EAF, kibuzzard-63D97EAF#2: G***; kibuzzard-63D97EAF
kibuzzard-64A91BF0: G***; kibuzzard-64A91BF0
kibuzzard-64A91C1C: G***; kibuzzard-64A91C1C
kibuzzard-64A91C24: G***; kibuzzard-64A91C24
kibuzzard-643EE5B9: G***; kibuzzard-643EE5B9
kibuzzard-643EE600: G***; kibuzzard-643EE600
kibuzzard-644014FA: G***; kibuzzard-644014FA

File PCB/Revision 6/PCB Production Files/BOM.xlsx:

﻿Designator | Value | Footprint | LCSC Part #
C1,C9,C10,C12,C17,C20,C22,C23,C24,C26,C29 | 100nF | C_0603_1608Metric | C1591
C2,C4,C15 | 1uF | C_0603_1608Metric | C15849
C3,C5,C6,C7,C8,C11,C13,C16,C18,C21,C25,C28 | 10uF | C_0805_2012Metric | C15850
D1 | BAT20J | D_SOD-323 | C49238173
D2 | SFH4547 | LED_5mm_Side_Mount | C405273
D3,D4,D5 | LED | LED_0603_1608Metric | C965807
D6,D7,D8,D9,D10,D11,D12,D13,D14,D15,D16 | LED | LED_0603_1608Metric | C84265
F1 | 1000mA | Fuse_1206_3216Metric_Pad1.42x1.75mm_HandSolder | C220146
J1 | USB_C_Receptacle_USB2.0 | USB_C_Receptacle_HRO_TYPE-C-31-M-12 | C2982555
J2 | Conn_01x50 | TFT_2.83IN_240X320_50PIN | C11098
J3,J7 | JST_PH_B2B-PH | JST_PH_B2B-PH-SM4-TB_1x02-1MP_P2.00mm_Vertical | C160352
J5 | Micro_SD_Card | MicroSD Slot TF-01A | C20613191
J6 | ER-CON06HB-1_TOUCH | ER-CON06HB-1_Compatible_1x06_P0.50mm_BottomContact | C202118
Q1,Q3,Q4,Q5,Q7 | DMG2301L | SOT-23 | C102619
Q2 | MBT3904DW1 | SOT-363_SC-70-6 | C110150
Q6 | FS8205A | SOT-23-6 | C908265
R1,R5,R23,R31,R32,R33,R34,R35,R38,R39,R40,R41,R42,R43,R44 | 2k2 | R_0603_1608Metric | C114662
R2,R3,R27,R28,R29 | 1k | R_0603_1608Metric | C22548
R4 | 100 | R_0603_1608Metric | C125923
R6,R10,R13,R14,R19,R20,R22,R24,R25,R26,R30,R36,R37 | 10k | R_0603_1608Metric | C98220
R7,R9 | 5.1k | R_0603_1608Metric | C105580
R8 | 1K2 | R_0603_1608Metric | C22765
R11,R12 | 4k7 | R_0603_1608Metric | C99782
R15,R16,R17,R18 | 10 | R_0603_1608Metric | C109318
R21 | 3R3 | R_0805_2012Metric | C313912
R45,R46,R47 | 4k7 | R_0603_1608Metric | C23162
S1,S2,S3,S4,S5,S6,S7,S8,S9,S10,S11,S12,S13,S14,S15,S16,S17,S18,S19,S20,S22,S23,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 | TL3342F160QG | SW_SPST_TL3342 | C778172
U1 | DW01A | SOT-23-6 | C18164398
U2 | XC6220B331 | SOT-23-5 | C86534
U3 | CH340C | SOIC-16_3.9x9.9mm_P1.27mm | C84681
U4 | USBLC6-2P6 | SOT-666 | C2827693
U5 | LIS3DHTR | XDCR_LIS3DHTR | C15134
U6 | TSSP77038 | Heimdall vertical | C3291489
U7 | ESP32-S3-WROOM-1-N16R8 | ESP32-S3-WROOM-1 | C2913202
U8 | AP2112K-3.3 | SOT-23-5 | C51118
U9 | MAX17048G | TDFN-8-1EP_2x2mm_P0.5mm_EP0.8x1.2mm | C2682616
U11 | TP4056 | Infineon_PG-DSO-8-27_3.9x4.9mm_EP2.65x3mm | C725790
U12 | TCA8418 | HVQFN-24-1EP_4x4mm_P0.5mm_EP2.5x2.5mm | C138713

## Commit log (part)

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2025-04-06 fixed mention of rev 4
